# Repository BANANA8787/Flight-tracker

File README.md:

# Flight tracker
A small device on a PCB that displays flights in the nearby area.
## Description
A PCB project powered by an ESP32. It uses a ILI9341 screen.
It has 4 navigation buttons for moving around the map, up, down, left and right. 
It also has a rotary encoder by the buttons, so you can zoom in and out. 
The screen is decently large, and it is able to be used as a touchscreen if I want to add some of that functionality later.
## Screenshots

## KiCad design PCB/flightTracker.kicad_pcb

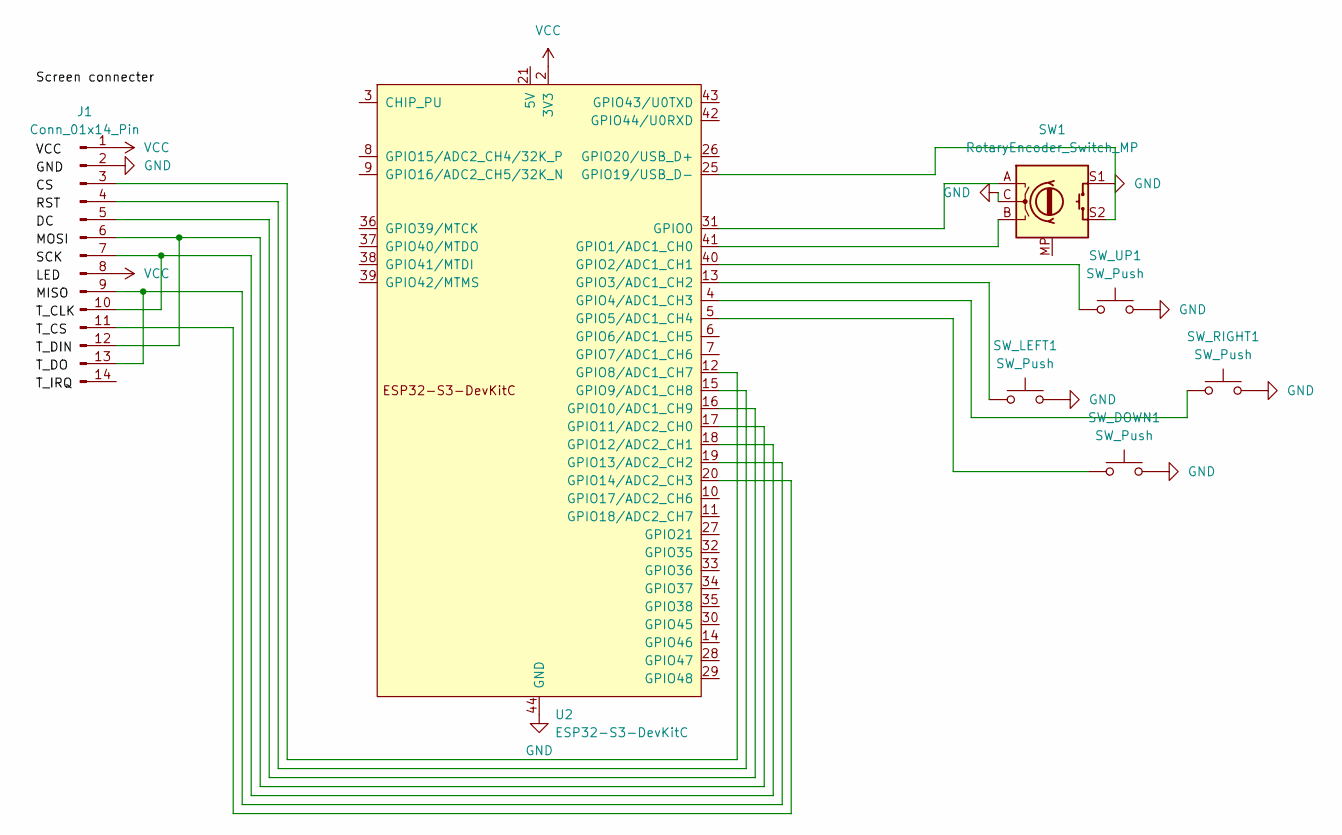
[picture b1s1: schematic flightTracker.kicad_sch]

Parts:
J1: Conn_01x14_Pin; PinHeader_1x14_P2.54mm_Vertical
SW1: RotaryEncoder_Switch_MP; RotaryEncoder_Alps_EC11E-Switch_Vertical_H20mm
SW_DOWN1: SW_Push; SW_PUSH_6mm
SW_LEFT1: SW_Push; SW_PUSH_6mm
SW_RIGHT1: SW_Push; SW_PUSH_6mm
SW_UP1: SW_Push; SW_PUSH_6mm
U2: ESP32-S3-DevKitC

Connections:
GND: J1.2, SW1.C, SW1.S1, SW_DOWN1.2, SW_LEFT1.2, SW_RIGHT1.2, SW_UP1.2, U2.22 (GND), U2.23 (GND), U2.24 (GND), U2.44 (GND)
unnamed: J1.3, U2.12 (GPIO8/ADC1_CH7)
unnamed: J1.4, U2.15 (GPIO9/ADC1_CH8)
unnamed: J1.5, U2.16 (GPIO10/ADC1_CH9)
unnamed: J1.7, J1.10, U2.18 (GPIO12/ADC2_CH1)
unnamed: J1.11, U2.20 (GPIO14/ADC2_CH3)
unnamed: J1.6, J1.12, U2.17 (GPIO11/ADC2_CH0)
unnamed: J1.9, J1.13, U2.19 (GPIO13/ADC2_CH2)
unnamed: SW1.A, U2.31 (GPIO0)
unnamed: SW1.B, U2.41 (GPIO1/ADC1_CH0)
unnamed: SW_UP1.1, U2.40 (GPIO2/ADC1_CH1)
unnamed: SW_LEFT1.1, U2.13 (GPIO3/ADC1_CH2)
unnamed: SW_RIGHT1.1, U2.4 (GPIO4/ADC1_CH3)
unnamed: SW_DOWN1.1, U2.5 (GPIO5/ADC1_CH4)
unnamed: SW1.S2, U2.25 (GPIO19/USB_D-)
VCC: J1.1, J1.8, U2.1 (3V3), U2.2 (3V3)

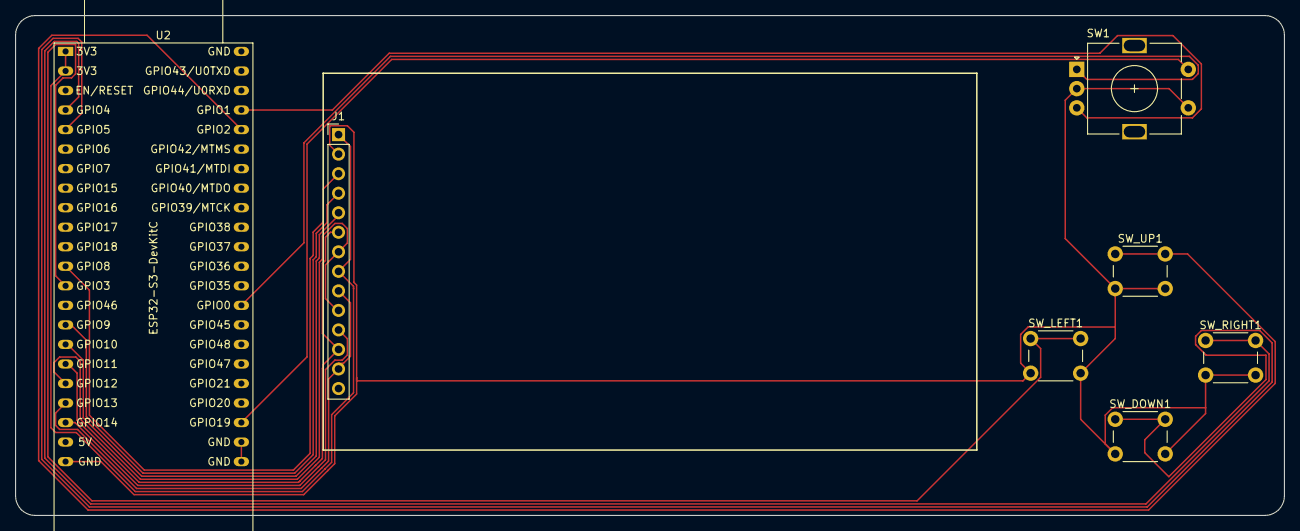
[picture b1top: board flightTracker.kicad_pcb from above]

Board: 2 copper layers, 165.0 x 65.0 mm, 7 parts (0 on the bottom side), 16 nets.
